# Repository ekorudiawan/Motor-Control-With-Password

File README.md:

# Motor-Control-With-Password
Motor Control With Simple Password Using Keypad 4x4

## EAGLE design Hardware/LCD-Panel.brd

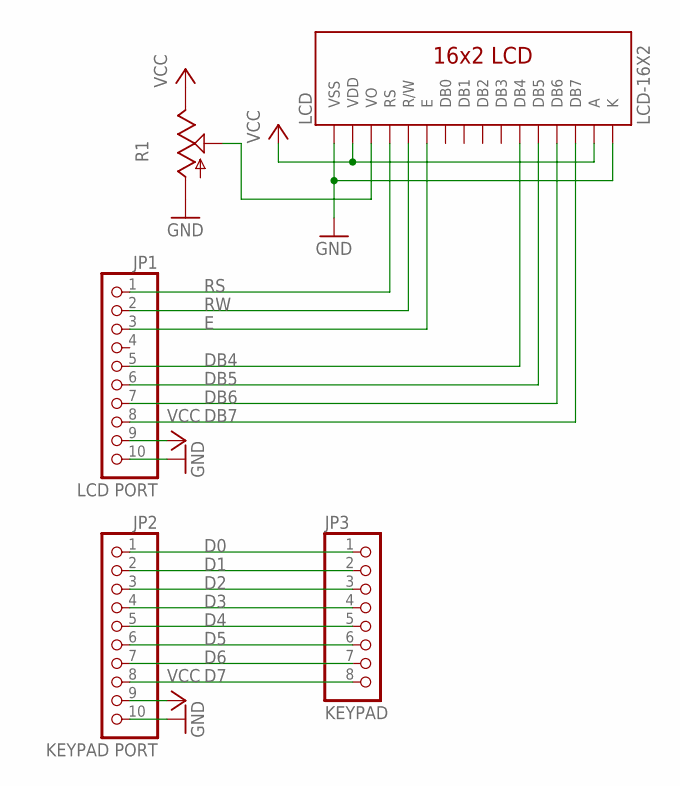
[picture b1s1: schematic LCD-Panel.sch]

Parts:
JP1: LCD PORT; 1X10
JP2: KEYPAD PORT; 1X10
JP3: KEYPAD; 1X08
LCD: LCD-16X2
R1: TRIMPOTCA6V; CA6V

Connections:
D0: JP2.1, JP3.1
D1: JP2.2, JP3.2
D2: JP2.3, JP3.3
D3: JP2.4, JP3.4
D4: JP2.5, JP3.5
D5: JP2.6, JP3.6
D6: JP2.7, JP3.7
D7: JP2.8, JP3.8
DB4: JP1.5, LCD.11 (DB4)
DB5: JP1.6, LCD.12 (DB5)
DB6: JP1.7, LCD.13 (DB6)
DB7: JP1.8, LCD.14 (DB7)
E: JP1.3, LCD.6 (E)
GND: JP1.10, JP2.10, LCD.1 (VSS), LCD.16 (K), R1.A
unnamed: LCD.3 (VO), R1.S
RS: JP1.1, LCD.4 (RS)
RW: JP1.2, LCD.5 (R/W)
VCC: JP1.9, JP2.9, LCD.2 (VDD), LCD.15 (A), R1.E

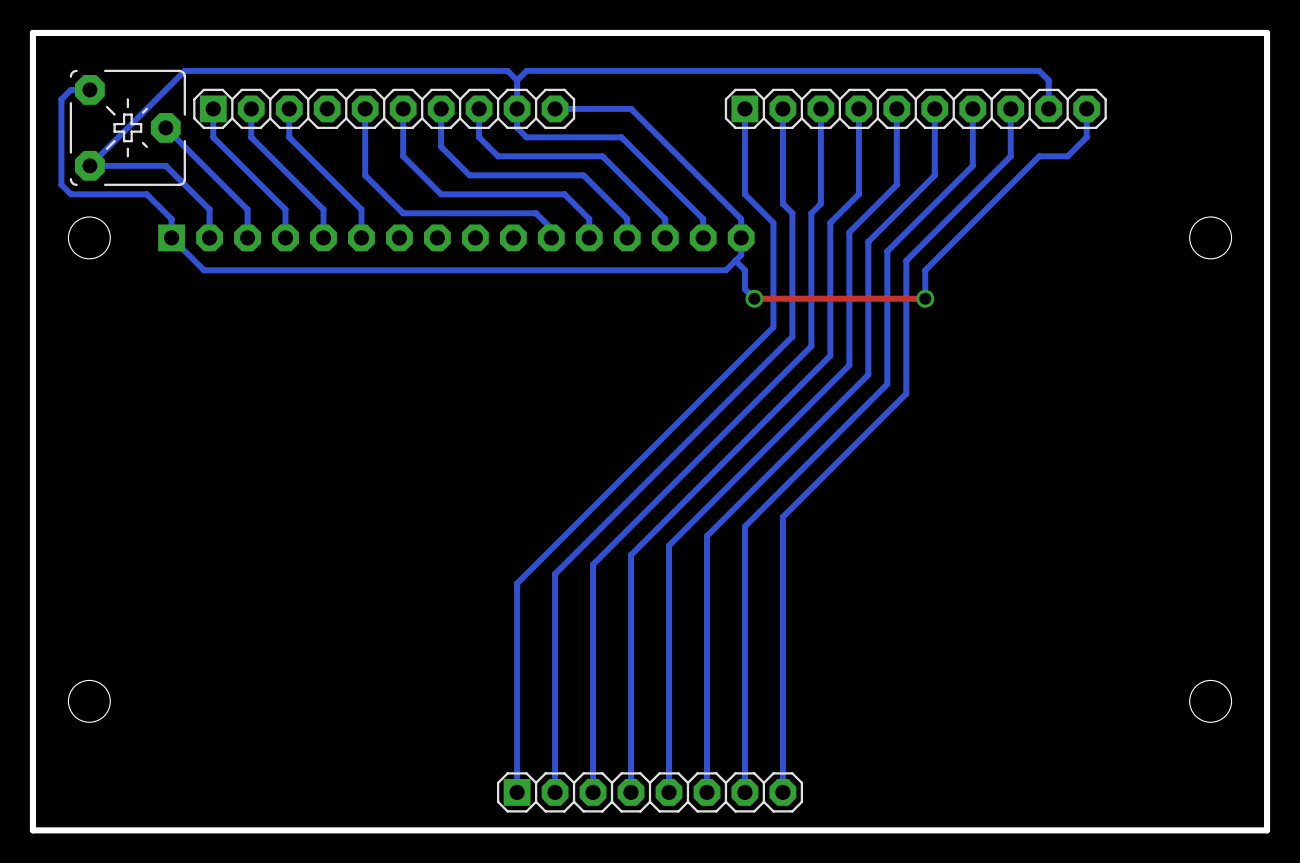
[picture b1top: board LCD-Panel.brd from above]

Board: 2 copper layers, 82.6 x 53.3 mm, 5 parts (0 on the bottom side), 18 nets.

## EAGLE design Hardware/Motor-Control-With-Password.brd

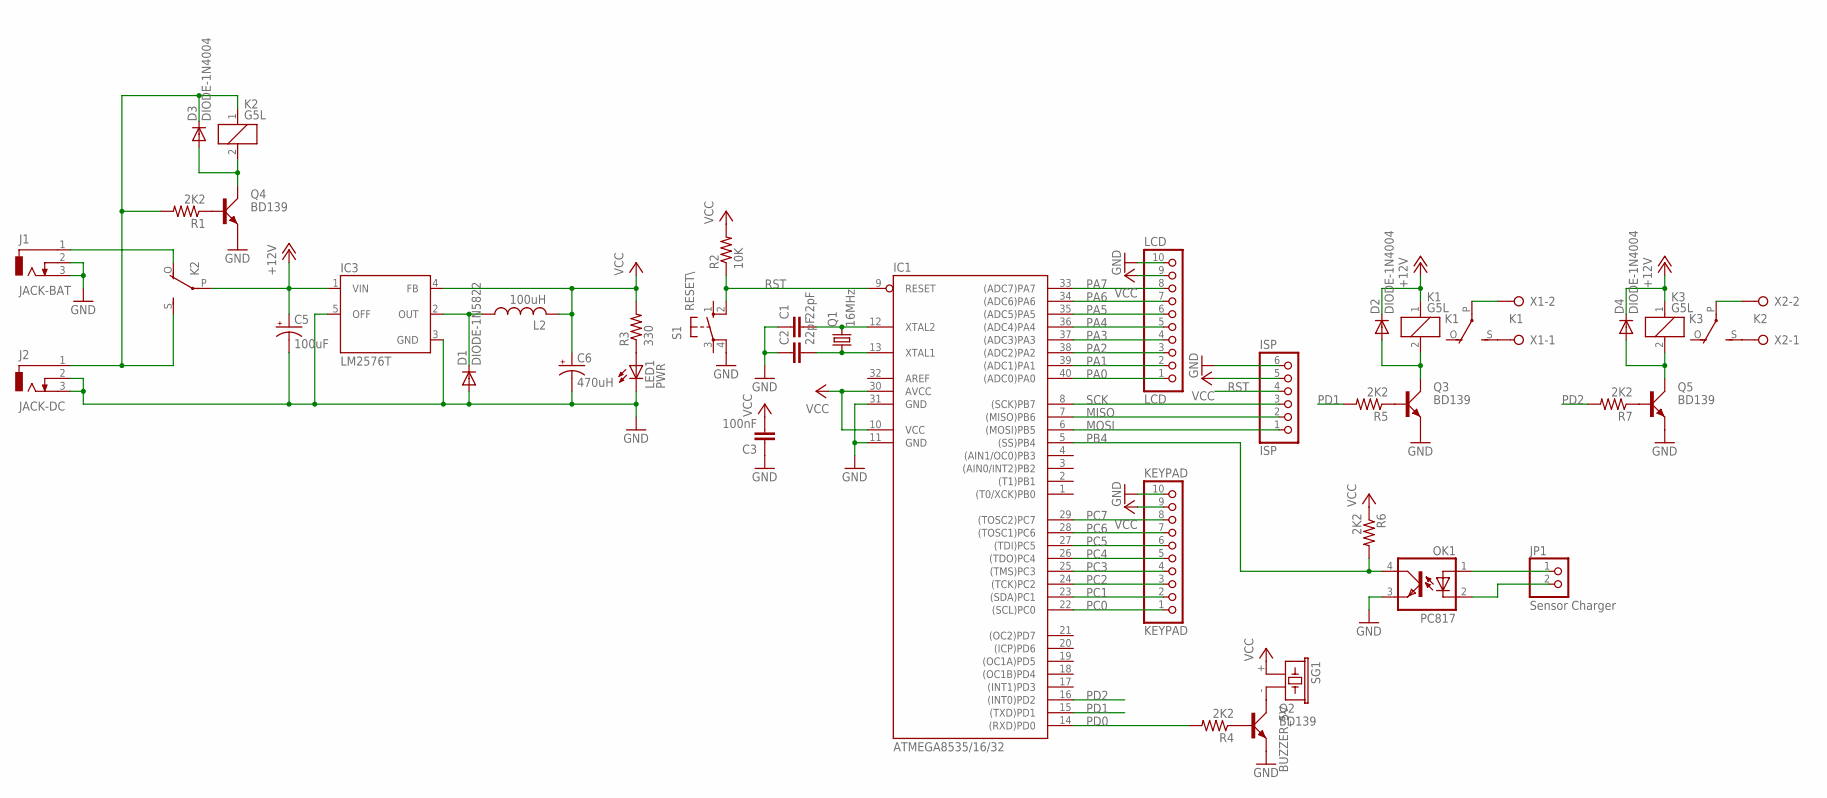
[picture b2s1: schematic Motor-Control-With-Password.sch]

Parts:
C1, C2: 22pF; C025-024X044
C3: 100nF; C025-024X044
C5: 100uF; E2,5-6
C6: 470uH; E3,5-8
D1: DIODE-1N5822; DO201-15
D2, D3, D4: DIODE-1N4004; DO41-10
IC1: ATMEGA8535/16/32; DIL40
IC3: LM2576T; TO220-5
ISP: ISP; 1X06
J1: JACK-BAT; DCJ0202
J2: JACK-DC; DCJ0202
JP1: Sensor Charger; 1X02
K1, K2, K3: G5L; G5LE
KEYPAD: KEYPAD; 1X10
L2: 100uH; TJ3-U2
LCD: LCD; 1X10
LED1: PWR; LED3MM
OK1: PC817; DIL04
Q1: 16MHz; HC49/S
Q2, Q3, Q4, Q5: BD139; TO126AV
R1, R4, R5, R6, R7: 2K2; 0207/10
R2: 10K; 0207/10
R3: 330; 0207/10
S1: RESET\; B3F-10XX
SG1: BUZZER_5V; BUZZER_F/CM12P
X1: K1; W237-132
X2: K2; W237-132

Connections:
+12V: C5.+, D2.C, D4.C, IC3.1 (VIN), K1.1, K2.P, K3.1
GND: C1.1, C2.1, C3.1, C5.-, C6.-, D1.A, IC1.11 (GND), IC1.31 (GND), IC3.3 (GND), IC3.5 (OFF), ISP.6, J1.2, J1.3, J2.2, J2.3, KEYPAD.10, LCD.10, LED1.K (C), OK1.3 (EMIT), Q2.E, Q3.E, Q4.E, Q5.E, S1.4 (P1)
MISO: IC1.7 ((MISO)PB6), ISP.2
MOSI: IC1.6 ((MOSI)PB5), ISP.1
unnamed: K1.S, X1.1
unnamed: C1.2, IC1.12 (XTAL2), Q1.2
unnamed: C2.2, IC1.13 (XTAL1), Q1.1
unnamed: Q4.B, R1.1
unnamed: D3.A, K2.2, Q4.C
unnamed: D1.C, IC3.2 (OUT), L2.1
unnamed: D3.C, J2.1, K2.1, K2.S, R1.2
unnamed: Q2.B, R4.1
unnamed: Q3.B, R5.1
unnamed: LED1.A, R3.1
unnamed: J1.1, K2.O
unnamed: JP1.1, OK1.1 (A)
unnamed: Q2.C, SG1.- (2)
unnamed: D2.A, K1.2, Q3.C
unnamed: JP1.2, OK1.2 (C)
unnamed: K1.P, X1.2
unnamed: Q5.B, R7.1
unnamed: D4.A, K3.2, Q5.C
unnamed: K3.S, X2.1
unnamed: K3.P, X2.2
PA0: IC1.40 ((ADC0)PA0), LCD.1
PA1: IC1.39 ((ADC1)PA1), LCD.2
PA2: IC1.38 ((ADC2)PA2), LCD.3
PA3: IC1.37 ((ADC3)PA3), LCD.4
PA4: IC1.36 ((ADC4)PA4), LCD.5
PA5: IC1.35 ((ADC5)PA5), LCD.6
PA6: IC1.34 ((ADC6)PA6), LCD.7
PA7: IC1.33 ((ADC7)PA7), LCD.8
PB4: IC1.5 ((SS)PB4), OK1.4 (COL), R6.2
PC0: IC1.22 ((SCL)PC0), KEYPAD.1
PC1: IC1.23 ((SDA)PC1), KEYPAD.2
PC2: IC1.24 ((TCK)PC2), KEYPAD.3
PC3: IC1.25 ((TMS)PC3), KEYPAD.4
PC4: IC1.26 ((TDO)PC4), KEYPAD.5
PC5: IC1.27 ((TDI)PC5), KEYPAD.6
PC6: IC1.28 ((TOSC1)PC6), KEYPAD.7
PC7: IC1.29 ((TOSC2)PC7), KEYPAD.8
PD0: IC1.14 ((RXD)PD0), R4.2
PD1: IC1.15 ((TXD)PD1), R5.2
PD2: IC1.16 ((INT0)PD2), R7.2
RST: IC1.9 (RESET), ISP.4, R2.1, S1.2 (S1)
SCK: IC1.8 ((SCK)PB7), ISP.3
VCC: C3.2, C6.+, IC1.10 (VCC), IC1.30 (AVCC), IC3.4 (FB), ISP.5, KEYPAD.9, L2.2, LCD.9, R2.2, R3.2, R6.1, SG1.+ (1)

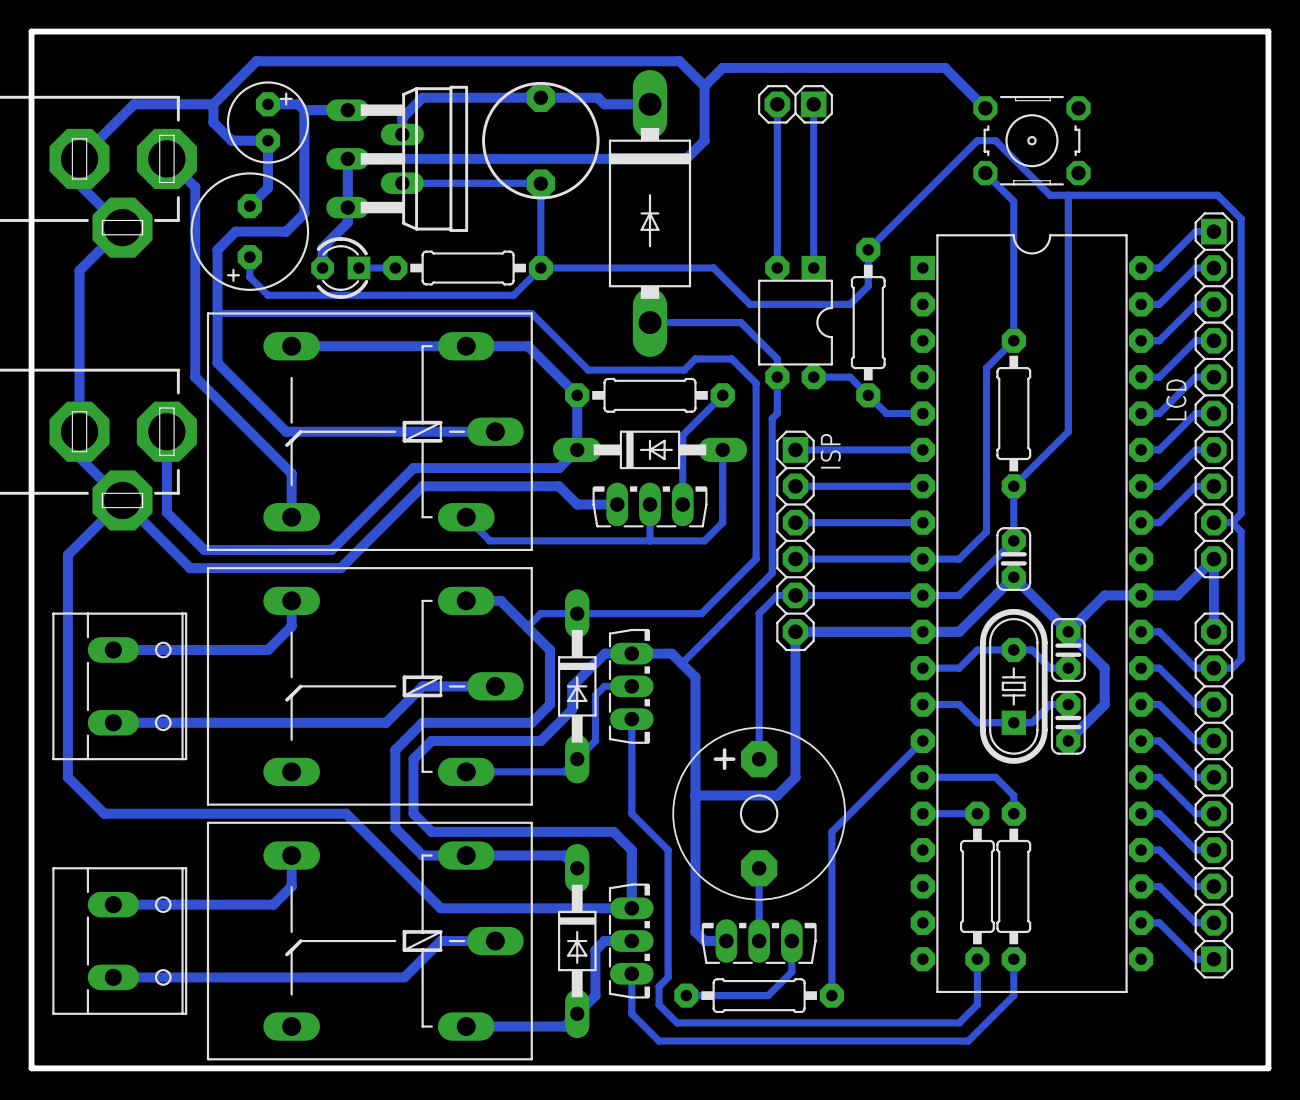
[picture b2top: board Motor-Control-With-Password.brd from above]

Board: 2 copper layers, 86.4 x 72.4 mm, 39 parts (0 on the bottom side), 47 nets.

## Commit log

2017-10-03 Added HW and SW Source Files
